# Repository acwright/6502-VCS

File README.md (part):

6502-VCS
========

An **AC6502** retro-style 8-bit computer based on the **65C02** microprocessor.

> 📖 **Guide:** [AC6502 Documentation](https://acwright.github.io/6502-DOCS/) — the user's and programmer's guide for the whole family.
> See [VCS's page in the family appendix](https://acwright.github.io/6502-DOCS/family/vcs).

---

**Building one? Every part you need, with supplier numbers and known issues, is in [BOM.md](BOM.md).**

## Table of Contents

- [Overview](#overview)
- [Architecture](#architecture)
- [Systems](#systems)
- [Software](#software)
- [Hardware](#hardware)
  - [Main Board](#main-board)
  - [Input Board](#input-board)
  - [Output Board](#output-board)
  - [ROM Cart](#rom-cart)
  - [Flash Cart](#flash-cart)
  - [Flash Helper](#flash-helper)
- [Which revision to make](#which-revision-to-make)
- [Firmware](#firmware)
  - [IB Controller](#ib-controller)
- [CAD](#cad)
- [Production](#production)
- [Schematics](#schematics)
- [Shared lines](#shared-lines)
- [Extra pins: `EXP0`–`EXP3` and `HRDB`](#extra-pins-exp0exp3-and-hrdb)
- [Jumpers](#jumpers)
- [Off-board headers](#off-board-headers)
- [Libraries](#libraries)
- [Bill of Materials](#bill-of-materials)
- [License](#license)

---

## Overview

The AC6502 ecosystem is a family of open-source, 65C02-based computers sharing a common architecture, memory map, and [BIOS](https://github.com/acwright/6502-BIOS). Each computer in the family is purpose-built for a different use case but runs the same software and firmware.

The **VCS** is a cartridge-based retro gaming console. It features a real 65C02 CPU, swappable ROM cartridges, VGA video output via [Pico9918](https://github.com/visrealm/pico9918), SID audio via ARMSID, and support for PS/2 keyboards, matrix keyboards, and Atari 2600-compatible joysticks.

## Architecture

All AC6502 computers share:

- **CPU**: 65C02 (or accurate emulation)
- **Memory**: 32KB RAM + 32KB ROM, with optional banked RAM expansion
- **Memory Map**: Standardized across the ecosystem — zero page, stack, I/O space ($8000–$9FFF), system ROM, and interrupt vectors at $FFFA–$FFFF
- **Bus**: 16-bit address bus, 8-bit bidirectional data bus, standard 65C02 control signals (RW, PHI2, RESET, IRQ, NMI, RDY, SYNC)
- **BIOS**: A common [BIOS](https://github.com/acwright/6502-BIOS) provides the kernel, monitor, and BASIC interpreter across all systems

## Systems

| Project | Description |
|---------|-------------|
| [6502-ACE](https://github.com/acwright/6502-ACE) | All-in-one Computer Experience — A single board computer |
| [6502-COB](https://github.com/acwright/6502-COB) | Computer On a Backplane — Modular desktop computer with expandable card slots |
| [6502-DEV](https://github.com/acwright/6502-DEV) | Development Environment Vehicle — Emulation-based dev system |
| [6502-KIM](https://github.com/acwright/6502-KIM) | Keypad Input Monitor - KIM-1 inspired minimal computer |
| [6502-VCS](https://github.com/acwright/6502-VCS) | Video Computer System — Cartridge-based retro gaming console (YOU ARE HERE) |

## Software

| Project | Description |
|---------|-------------|
| [6502-BIOS](https://github.com/acwright/6502-BIOS) | The shared BIOS (kernel, monitor, BASIC) for all AC6502 computers |
| [6502-EMULATOR](https://github.com/acwright/6502-EMULATOR) | Emulator for the whole family — desktop app, browser build, and a command line for scripted runs |
| [6502-PRG](https://github.com/acwright/6502-PRG) | Template project for writing assembly language programs |
| [6502-CRT](https://github.com/acwright/6502-CRT) | Template project for writing assembly language cartridges |
| [6502-ASM](https://github.com/acwright/6502-ASM) | Assembly language example programs and demos |
| [6502-BAS](https://github.com/acwright/6502-BAS) | BASIC program listings |
| [6502-WOZMON](https://github.com/acwright/6502-WOZMON) | Wozmon as a standalone ROM |
| [6502-NOP](https://github.com/acwright/6502-NOP) | An all-NOP ROM, for probing a board during bring-up |
| [6502-DOCS](https://github.com/acwright/6502-DOCS) | The documentation site — the guide, the printable reference cards, branding and label artwork |
| [cffs](https://github.com/acwright/cffs) | Builds CompactFlash disk images for the BIOS filesystem |
| [bastok](https://github.com/acwright/bastok) | Tokenizes BASIC listings into `.prg` images, and back |
| [bin2woz](https://github.com/acwright/bin2woz) | Converts a binary into a Wozmon serial upload |

## Hardware

This repository contains KiCad 7.0+ PCB designs for the boards that make up the VCS system.

### Main Board
`Hardware/Main Board/`

The core board containing the 65C02 CPU, 32KB SRAM, 32KB EEPROM, clock, and reset circuitry. Runs at 1 MHz and provides the bus connection for the Input and Output boards.

### Input Board
`Hardware/Input Board/`

Unified input board supporting a matrix keyboard, PS/2 keyboard, and Atari 2600-compatible joysticks. Uses a 65C22 VIA and an ATmega1284 microcontroller as the keyboard encoder controller.

The joysticks share the VIA ports with the keyboard encoder rather than having connectors of their own: they come in on the `J1` PORT B and `J2` PORT A box headers, with `JOY(1)` reading PORT B and `JOY(2)` reading PORT A. See [Joystick Interface](./Firmware/IB%20Controller/README.md#joystick-interface) for the wiring options and the bitmask the BIOS returns.

### Output Board
`Hardware/Output Board/`

Combined VGA video output (via Raspberry Pi Pico running [Pico9918](https://github.com/visrealm/pico9918)) and SID audio output (via ARMSID). Provides TMS9918A-compatible graphics modes at 640×480 VGA and 3-voice SID synthesis.

### ROM Cart
`Hardware/ROM Cart/`

Swappable ROM cartridge for the VCS system. Rev 1.0 came in two versions, one for each ROM chip:

- **Rev 1.0a** — Uses the **28C256** 32KB EEPROM (electrically erasable, no UV eraser required).
- **Rev 1.0b** — Uses the **27C256** 32KB EPROM (UV-erasable).

**Rev 1.1** (drawn, not yet made) takes either chip. Two solder jumpers, JP1 and JP2, ship set for the 28C256
(`28C`); cut and re-bridge both to `27C` for a 27C256. It also has an option for tinkerers, not fitted:
J2, `ROM BANK`, picks the chip's upper 16K (`HI`, as made) or its lower 16K (`LO`), so one chip can hold two
programs. See *Jumpers* below and the build notes in `BOM.md`.

### Flash Cart
`Hardware/Flash Cart/`

Banked flash cartridge, and the successor to the fixed 16K ROM Cart. One all-SMD board covers 128KB to 1MB,
depending on which parts are populated, and the flash is programmed in circuit through the card edge, either by
the Flash Helper (an Arduino Mega 2560 shield with one connector on it) or by the 6502 itself.

- `$C000–$DFFF` is a switchable 8K window, selected by a write-only bank register at `$E000–$FFFF`.
- `$E000–$FFFF` is fixed to the last 8K of the primary flash, so the vectors and the bank-switching code can
  never be mapped out.
- Existing 16K cart images run unmodified.
- **Tested in the 512KB and 1MB builds** (2026-11-09): programmed through the Flash Helper, and run on an ACE,
  banking into both chips and saving across a power cycle. The 128KB and 256KB builds (SST39SF010A, SST39SF020A)
  use the same board but haven't been built yet.
- Its 0.5 mm TSOP parts make it the hardest board in the family to build by hand: having JLCPCB assemble it is the
  preferred way to get one. See the build notes in [BOM.md](BOM.md#build-notes).

See [DESIGN.md](./Hardware/Flash%20Cart/Rev%201.0/DESIGN.md) for the memory map, the logic, the programming
sequences and the build variants.

### Flash Helper
`Hardware/Flash Helper/`

The programmer for the Flash Cart: an Arduino Mega 2560 R3 shield with a cartridge slot on it, and
nothing else. It pretends to be the 65C02 on the far side of the card edge, so a cart is programmed
in circuit with no chip ever removed — which matters, because the flash is a soldered-down TSOP part.

- Two parts: the Arduino, and the same TE card edge connector the Main Board fits as J9.
- Thirty-seven of the forty card edge pins: `A0–A15`, `D0–D7`, `RWB`, `PHI2`, `RESB`, `IRQB`, `NMIB`,
  `VCC` and `GND`.
- `EXP0` and `EXP1` are deliberately **not** connected. Cartridges tie them to GND to disable the
  system ROM, so driving them would be a short.
- Host side is `6502-flash`, a Node CLI. See [DESIGN.md](./Hardware/Flash%20Cart/Rev%201.0/DESIGN.md).

**As a card tester.** Every card in the AC6502 family — the [COB](https://github.com/acwright/6502-COB)
cards, the [KIM](https://github.com/acwright/6502-KIM) Keypad Card and both VCS carts — carries the same
`6502 Card Edge` fingers and drops into this socket. `IRQB` and `NMIB` are wired for that reason rather
than for programming: the GPIO, LCD, Serial and Serial Card Pro cards all assert `IRQB`, and a tester
that could not see it would miss most of what they do. That firmware is a separate build and does not
exist yet.

<!-- Which revision to make: generated by Tools/revision-audit/register.py from Tools/data/orders.json. Edit that file, not this section. -->
## Which revision to make

**Make the newest revision of a board, and check its label first.** The table below gives each board's newest revision. A newer revision fixes what was found on the older ones. Every revision, old and new, is in [REVISIONS.md](REVISIONS.md), with what changed in each.

Each revision carries one of three labels:

- **Tested:** This revision was built and tested.
- **Proven design:** Not built at this revision, but its circuit is a tested revision's. The only changes are silkscreen text, part values, mounting holes, outline clean-up, parts moved a fraction of a millimetre onto their grid, capacitor pitch, socket outlines, a footprint swap with the same holes, a solder jumper's default, the solder mask or paste at a card edge, or tracks rerouted or pours refilled with DRC and the netlist check passing. A builder can treat it as tested.
- **Untested:** The circuit, the power path or the layout changed in a way that only a built board proves, or the board has never been built at all.

[BOM.md](BOM.md) has the parts for every revision, and its known issues.

| Board | Newest revision | Label | Why |
|---|---|---|---|
| Flash Cart | 1.1 | **Proven design** | The bare card edge and the shell's holes at their nominal places. |
| Flash Helper | 1.1 | **Proven design** | J1's reference resized and the logo moved; silkscreen only. |
| Input Board | 1.1 | **Proven design** | Silkscreen text only. |
| Main Board | 1.1 | **Proven design** | 10k pull-ups, small part moves and tracks rerouted, and a 74HCT00 at U5. The jumpers are gone, and `HRDB` is wired as it is on the tested Rev 1.0 with them fitted. |
| Output Board | 1.1 | **Proven design** | Silkscreen text, the `VDD` header removed, JP1 ships open, and JP2 and JP3 removed and wired as Rev 1.0 ships them. |
| ROM Cart | 1.1 | **Proven design** | Either ROM chip through two solder jumpers, each setting a tested board's wiring; a ROM bank option, not fitted, whose pull-up reads the half Rev 1.0 reads; capacitor pitch; the bare card edge and the shell's holes at their nominal places. |
<!-- End of which revision to make -->

## Firmware

This repository contains [PlatformIO](https://platformio.org/)-based firmware for the Input Board.

### IB Controller
`Firmware/IB Controller/`

Firmware for the ATmega1284 on the Input Board. Provides:

- Matrix keyboard scanning and encoding
- PS/2 keyboard interface
- Atari 2600-compatible joystick input
- Parallel I/O to the AC6502 bus via 65C22 VIA

See [Firmware/IB Controller/README.md](./Firmware/IB%20Controller/README.md) for setup and usage instructions.

## CAD
`CAD/`

3D-printable enclosure parts and laser-cut top panels for the VCS system.

**Board images** are in `CAD/Images/<Board>/Rev X/`: `Front.png` and `Back.png` on white, and `Front Transparent.png` and `Back Transparent.png` with no background. Every image is a 3D render at the same size, with the black solder mask and white silkscreen the boards are made with. Bare-board photos may differ, because the renders show parts fitted.

**Top panels are versioned by board revision**, like `Hardware/`: `CAD/Tops/<Board>/Rev X/`. Each revision has its own complete folder, even when two revisions share the same files. `Bases/` holds the parts for a whole computer, not for one board, so it isn't versioned.

The **[plate mounting drawing](CAD/Bases/Plate%20Mounting%20Drawing.png)** ([SVG](CAD/Bases/Plate%20Mounting%20Drawing.svg)) shows where the Output Board, the Main Board and the Input Board mount on the base plate, with every hole's position and the hardware the build needs. The plate is a stack of three 3 mm acrylic layers.

## Production
`Production/`

[REVISIONS.md](REVISIONS.md) lists every board revision: whether it was made, its JLCPCB order, the commit it was made from, and what fits it.

JLCPCB-ready Gerber files and BOM/CPL for PCB fabrication and assembly.

## Schematics
`Schematics/`

PDF schematics for each board.

## Shared lines

Five lines of the 6502 bus are shared by every board on it: `RESB`, `IRQB`, `NMIB`, `RDY` and `BE`. A board may pull one of these lines low, and nothing drives one high. Each line is held high by one 10kΩ pull-up resistor to VCC, on the board with the CPU: the ACE Board, the KIM Board, the VCS Main Board, the COB CPU Card or CPU Card Pro, or the DEV Board. No other board has one. Two pull-ups on the same line would sit in parallel and lower its resistance, so a card that adds its own pull-up changes the machine for every other board. The VIAs and PIAs in the BOMs, the W65C22N and W65C21N, have open-drain interrupt outputs for this reason.

**Interrupt outputs.** Whatever drives `IRQB` or `NMIB` may only pull it low. Every board is drawn for the parts in its BOM and works as shipped, with no jumper to cut or bridge:

- **A part whose interrupt output is open-drain** (the W65C22N, W65C21N, R6551AP, DS1511Y and TMS9918A) drives the line directly, or through a diode with a solder jumper across it that ships bridged. The diode is fitted either way. To use a part that drives its interrupt high as well as low instead, such as a W65C22S or a replacement of your own, cut the jumper: the diode then lets the part only pull the line low. A board with no diode in the line can't take such a part.
- **A part that drives its interrupt high as well as low** (the pico9918, the VERA module, and a microcontroller such as the ATmega1284 or a Raspberry Pi Pico) reaches the line through a diode, a BAT85 or a 1N914, with its cathode toward the part. Where a solder jumper sits across that diode, it ships open. The diode is then the only path to the line, so fit it, and never bridge the jumper, because the part would then hold the line high against every other interrupt source.
- **A microcontroller wired to the line directly,** as on the ACE Board, the Mega Helper and the Flash Helper, drives it open-drain in its firmware: it sets the pin low or leaves it as an input, and never drives it high.

The *Jumpers* section below gives each board's interrupt jumper.

The same holds where a board has its own reset circuit. A reset switch, its timer and the transistor that pulls `RESB` low can be on any board, such as the COB Backplane Pro or the Clock Card, but the `RESB` pull-up is only ever on the board with the CPU. Each of those boards draws its pull-ups together, in one group on its schematic.

The DEV Board is the exception on `RESB`. It stands in for a Main Board, so it owns reset: its Reset button goes to the Teensy, and the Teensy drives `RESB` onto the bus through U3, a level shifter that only sends signals out, as it drives `PHI2`. U3 holds `RESB` high or low, so the DEV Board has no `RESB` pull-up, and nothing else on its bus may pull `RESB` low. Connect a DEV only to a passive backplane, never to the COB Backplane Pro, whose reset circuit would pull against U3, and don't fit a card that pulls `RESB` low, such as the COB RTC Card.

`SOB` is a CPU pin that isn't on the bus. It is tied to VCC, directly or through a 10kΩ resistor.

A few chips have a pull-up of their own inside the chip, such as an ATmega's reset pin. Where such a pin is wired to `RESB`, its pull-up of 30–60kΩ sits in parallel with the 10kΩ one. That's harmless, because whatever pulls `RESB` low can sink the extra current many times over.

A revision that doesn't follow this yet says so in its known issues in [BOM.md](BOM.md), with what to fit or remove.

## Extra pins: `EXP0`–`EXP3` and `HRDB`

`EXP` stands for "extra pin". Four pins of the 6502 bus are left for a builder's own use: pin 4 is `EXP1`, pin 6 is `EXP0`, pin 19 is `EXP3` and pin 21 is `EXP2`.

Pins 4 and 6 have a second job. A cartridge ties both of them to GND. That pulls `HRDB` ("High ROM disable bar", active low) low on the board with the ROM, which takes `$C000–$FFFF` away from the ROM so that the cartridge answers there instead. So in a build that uses cartridges, pins 4 and 6 are reserved for `HRDB`, and nothing else may drive them. They are free as `EXP1` and `EXP0` only in a build that never uses cartridges. `EXP2` and `EXP3` are always free.

How the boards treat pins 4 and 6:

- **The ACE Board and the KIM Board** join them to their ROM's `HRDB` input, and their silk says `HRDB`. The VCS Main Board joins them the same way from Rev 1.1.
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
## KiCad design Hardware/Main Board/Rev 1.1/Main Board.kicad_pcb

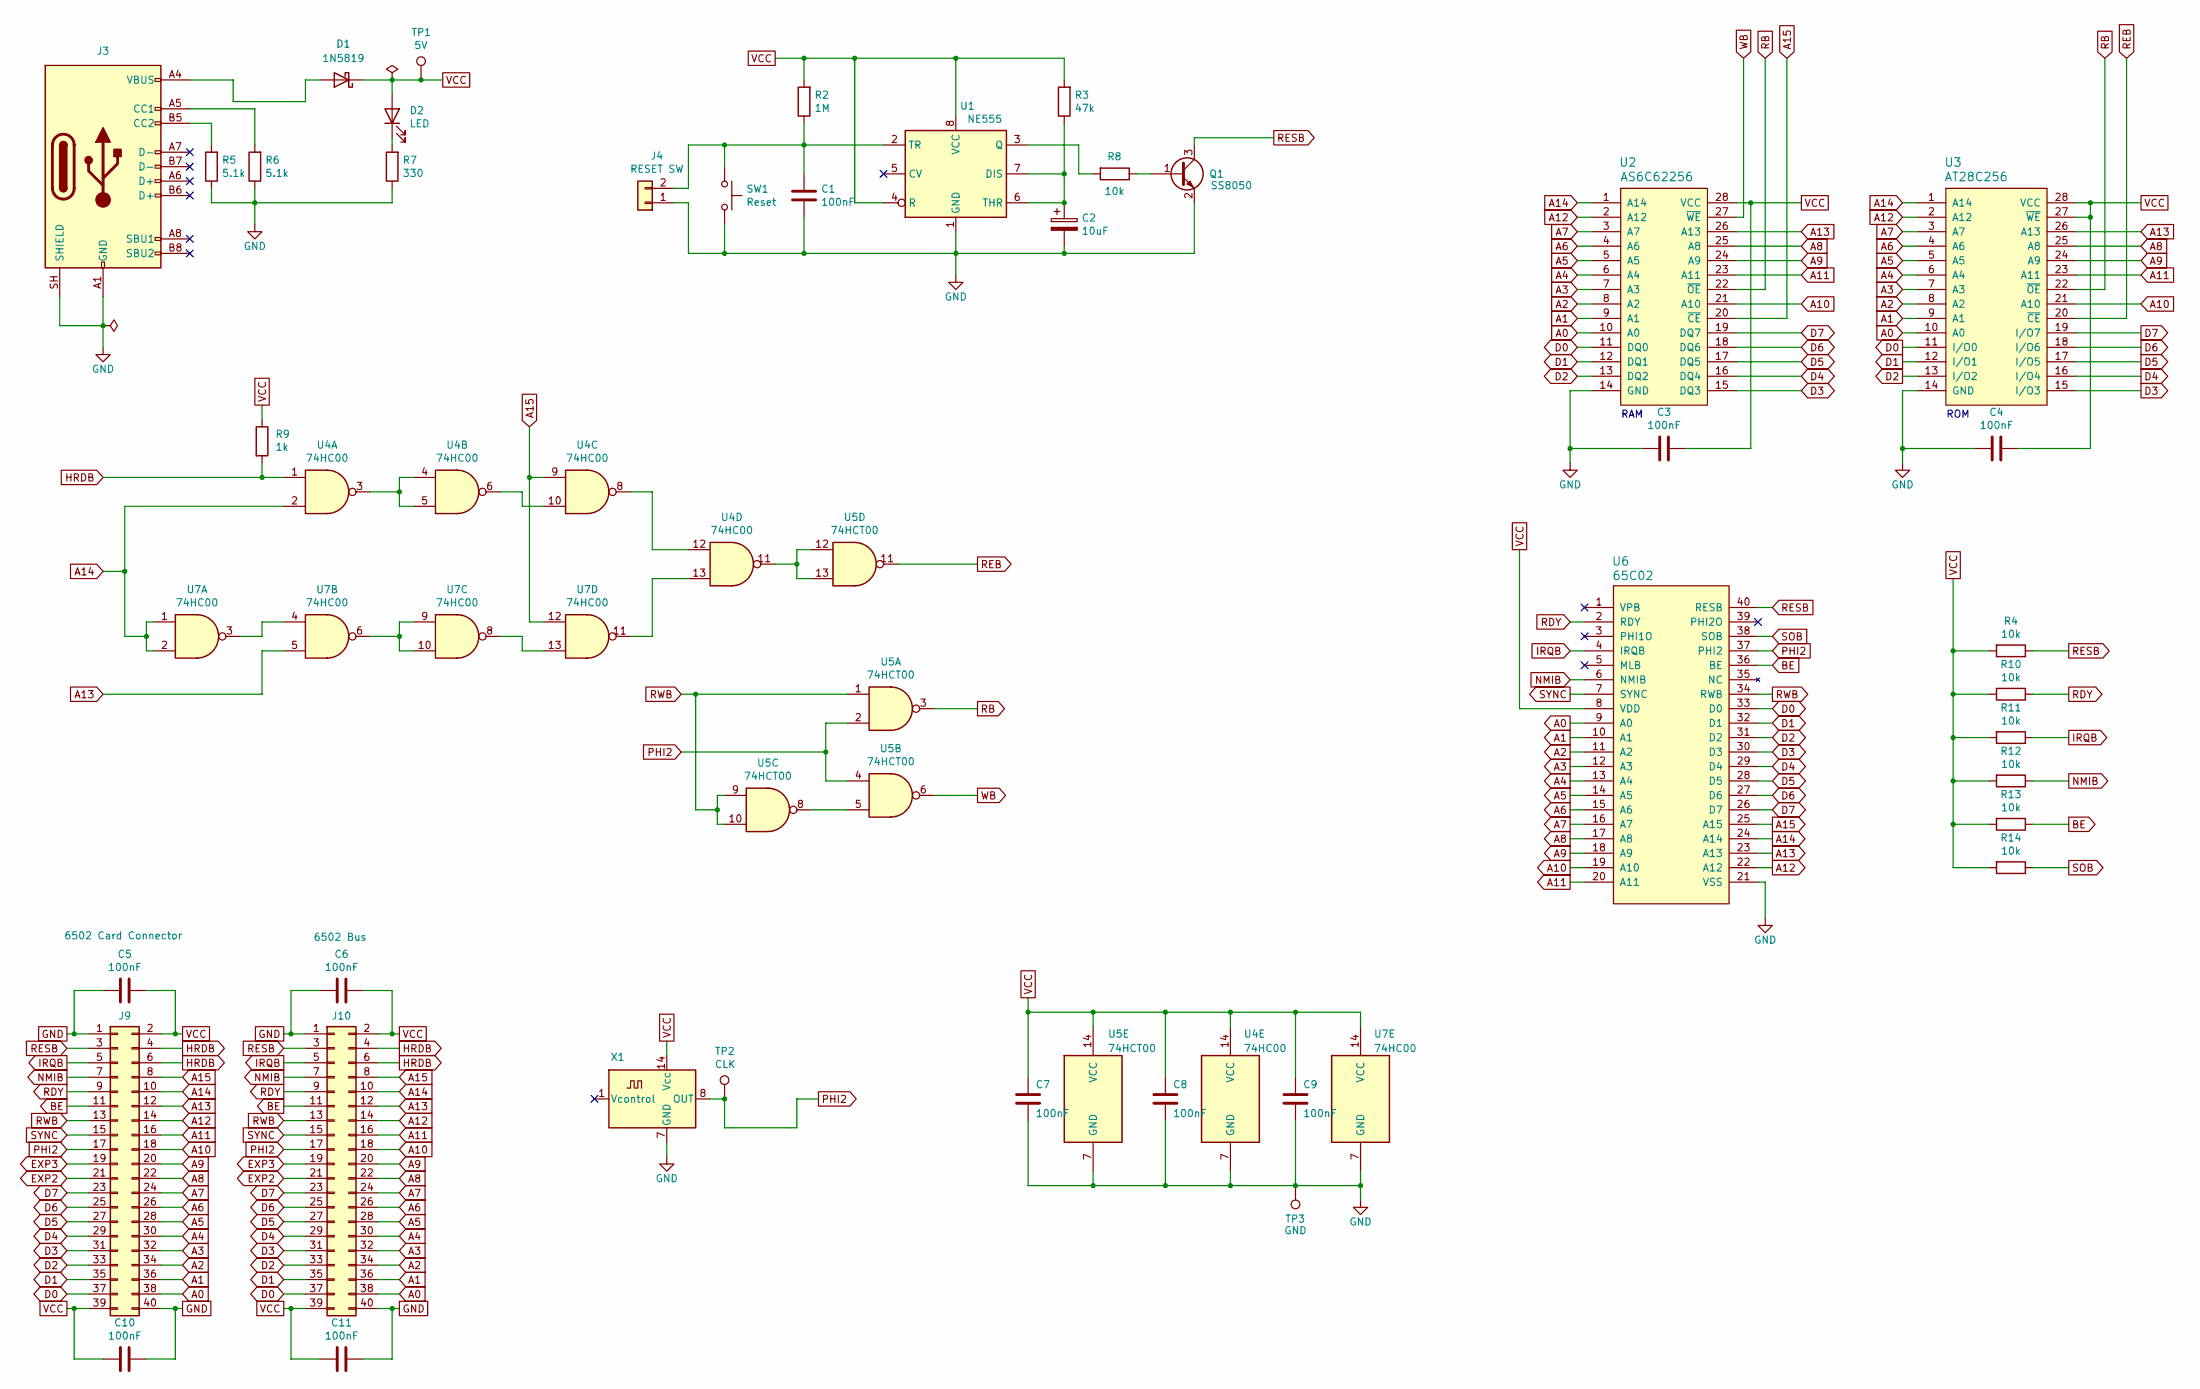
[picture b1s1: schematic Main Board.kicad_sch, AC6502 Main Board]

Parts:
C1, C3, C4, C5, C6, C7, C8, C9, C10, C11: 100nF; C_0805_2012Metric; LCSC C49678
C2: 10uF; C_1206_3216Metric; LCSC C7171
D1: 1N5819; D_SOD-323F; LCSC C191023
D2: LED; LED_0805_2012Metric; LCSC C2297
J3: USB_C_Receptacle_USB2.0; USB_C_Receptacle_HRO_TYPE-C-31-M-12; LCSC C2988369
J4: RESET SW; JST_XH_B2B-XH-A_1x02_P2.50mm_Vertical; Digikey 455-B2B-XH-A-ND
J9: 6502 Card Connector; 6502 Card Slot; Mouser 571-5-5530843-4
J10: 6502 Bus; 6502 Bus Connector; Digikey 732-5401-ND
Q1: SS8050; SOT-23; LCSC C2150
R2: 1M; R_0805_2012Metric; LCSC C17514
R3: 47k; R_0805_2012Metric; LCSC C17713
R4, R8, R10, R11, R12, R13, R14: 10k; R_0805_2012Metric; LCSC C17414
R5, R6: 5.1k; R_0805_2012Metric; LCSC C27834
R7: 330; R_0805_2012Metric; LCSC C17630
R9: 1k; R_0805_2012Metric; LCSC C17513
SW1: Reset; Tact Switch SMD 5.1mm; LCSC C318884
TP1: 5V; TestPoint_Pad_1.0x1.0mm
TP2: CLK; TestPoint_Pad_1.0x1.0mm
TP3: GND; TestPoint_Pad_1.0x1.0mm
U1: NE555; SOIC-8_3.9x4.9mm_P1.27mm; LCSC C7593
U2: AS6C62256; DIP-28_W15.24mm_Socket_LongPads; Digikey 1450-1033-ND
U3: AT28C256; DIP_Socket-28_W11.9mm_W12.7mm_W15.24mm_W17.78mm_W18.5mm_3M_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; Digikey AT28C256-15PU-ND
U4, U7: 74HC00; SOIC-14_3.9x8.7mm_P1.27mm; LCSC C5586
U5: 74HCT00; SOIC-14_3.9x8.7mm_P1.27mm; LCSC C6764
U6: 65C02; DIP-40_W15.24mm_Socket_LongPads; Mouser 955-W65C02S6TPG-14
X1: 1 MHz; Oscillator_DIP-14; Digikey X937-ND

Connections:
A0: J9.38, J10.38, U2.10 (A0), U3.10 (A0), U6.9 (A0)
A1: J9.36, J10.36, U2.9 (A1), U3.9 (A1), U6.10 (A1)
A2: J9.34, J10.34, U2.8 (A2), U3.8 (A2), U6.11 (A2)
A3: J9.32, J10.32, U2.7 (A3), U3.7 (A3), U6.12 (A3)
A4: J9.30, J10.30, U2.6 (A4), U3.6 (A4), U6.13 (A4)
A5: J9.28, J10.28, U2.5 (A5), U3.5 (A5), U6.14 (A5)
A6: J9.26, J10.26, U2.4 (A6), U3.4 (A6), U6.15 (A6)
A7: J9.24, J10.24, U2.3 (A7), U3.3 (A7), U6.16 (A7)
A8: J9.22, J10.22, U2.25 (A8), U3.25 (A8), U6.17 (A8)
A9: J9.20, J10.20, U2.24 (A9), U3.24 (A9), U6.18 (A9)
A10: J9.18, J10.18, U2.21 (A10), U3.21 (A10), U6.19 (A10)
A11: J9.16, J10.16, U2.23 (A11), U3.23 (A11), U6.20 (A11)
A12: J9.14, J10.14, U2.2 (A12), U3.2 (A12), U6.22 (A12)
A13: J9.12, J10.12, U2.26 (A13), U3.26 (A13), U6.23 (A13), U7.5
A14: J9.10, J10.10, U2.1 (A14), U3.1 (A14), U4.2, U6.24 (A14), U7.1, U7.2
A15: J9.8, J10.8, U2.20 (~CE), U4.9, U6.25 (A15), U7.12
BE: J9.11, J10.11, R13.1, U6.36 (BE)
D0: J9.37, J10.37, U2.11 (DQ0), U3.11 (I/O0), U6.33 (D0)
D1: J9.35, J10.35, U2.12 (DQ1), U3.12 (I/O1), U6.32 (D1)
D2: J9.33, J10.33, U2.13 (DQ2), U3.13 (I/O2), U6.31 (D2)
D3: J9.31, J10.31, U2.15 (DQ3), U3.15 (I/O3), U6.30 (D3)
D4: J9.29, J10.29, U2.16 (DQ4), U3.16 (I/O4), U6.29 (D4)
D5: J9.27, J10.27, U2.17 (DQ5), U3.17 (I/O5), U6.28 (D5)
D6: J9.25, J10.25, U2.18 (DQ6), U3.18 (I/O6), U6.27 (D6)
D7: J9.23, J10.23, U2.19 (DQ7), U3.19 (I/O7), U6.26 (D7)
EXP2: J9.21, J10.21
EXP3: J9.19, J10.19
GND: C1.2, C2.2, C3.2, C4.2, C5.2, C6.2, C7.2, C8.2, C9.2, C10.1, C11.1, J3.A1 (GND), J3.A12 (GND), J3.B1 (GND), J3.B12 (GND), J3.SH (SHIELD), J4.1, J9.1, J9.40, J10.1, J10.40, Q1.2 (E), R5.1, R6.1, R7.1, SW1.2, TP3.1 (1_1), U1.1 (GND), U2.14 (GND), U3.14 (GND), U4.7 (GND), U5.7 (GND), U6.21 (VSS), U7.7 (GND), X1.7 (GND)
HRDB: J9.4, J9.6, J10.4, J10.6, R9.2, U4.1
IRQB: J9.5, J10.5, R11.1, U6.4 (IRQB)
NMIB: J9.7, J10.7, R12.1, U6.6 (NMIB)
unnamed: D1.2 (A), J3.A4 (VBUS), J3.A9 (VBUS), J3.B4 (VBUS), J3.B9 (VBUS)
unnamed: D2.1 (K), R7.2
unnamed: J3.A5 (CC1), R6.2
unnamed: J3.B5 (CC2), R5.2
unnamed: C1.1, J4.2, R2.1, SW1.1, U1.2 (TR)
unnamed: Q1.1 (B), R8.1
unnamed: C2.1, R3.1, U1.6 (THR), U1.7 (DIS)
unnamed: R8.2, U1.3 (Q)
unnamed: U4.3, U4.4, U4.5
unnamed: U4.6, U4.10
unnamed: U4.11, U5.12, U5.13
unnamed: U4.8, U4.12
unnamed: U4.13, U7.11
unnamed: U5.5, U5.8
unnamed: U7.3, U7.4
unnamed: U7.6, U7.9, U7.10
unnamed: U7.8, U7.13
PHI2: J9.17, J10.17, TP2.1 (1_1), U5.2, U5.4, U6.37 (PHI2), X1.8 (OUT)
RB: U2.22 (~OE), U3.22 (~OE), U5.3
RDY: J9.9, J10.9, R10.1, U6.2 (RDY)
REB: U3.20 (~CE), U5.11
RESB: J9.3, J10.3, Q1.3 (C), R4.1, U6.40 (RESB)
RWB: J9.13, J10.13, U5.1, U5.9, U5.10, U6.34 (RWB)
SOB: R14.1, U6.38 (SOB)
SYNC: J9.15, J10.15, U6.7 (SYNC)
VCC: C3.1, C4.1, C5.1, C6.1, C7.1, C8.1, C9.1, C10.2, C11.2, D1.1 (K), D2.2 (A), J9.2, J9.39, J10.2, J10.39, R2.2, R3.2, R4.2, R9.1, R10.2, R11.2, R12.2, R13.2, R14.2, TP1.1 (1_1), U1.4 (R), U1.8 (VCC), U2.28 (VCC), U3.27 (~WE), U3.28 (VCC), U4.14 (VCC), U5.14 (VCC), U6.8 (VDD), U7.14 (VCC), X1.14 (Vcc)
WB: U2.27 (~WE), U5.6

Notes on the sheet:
ROM
RAM

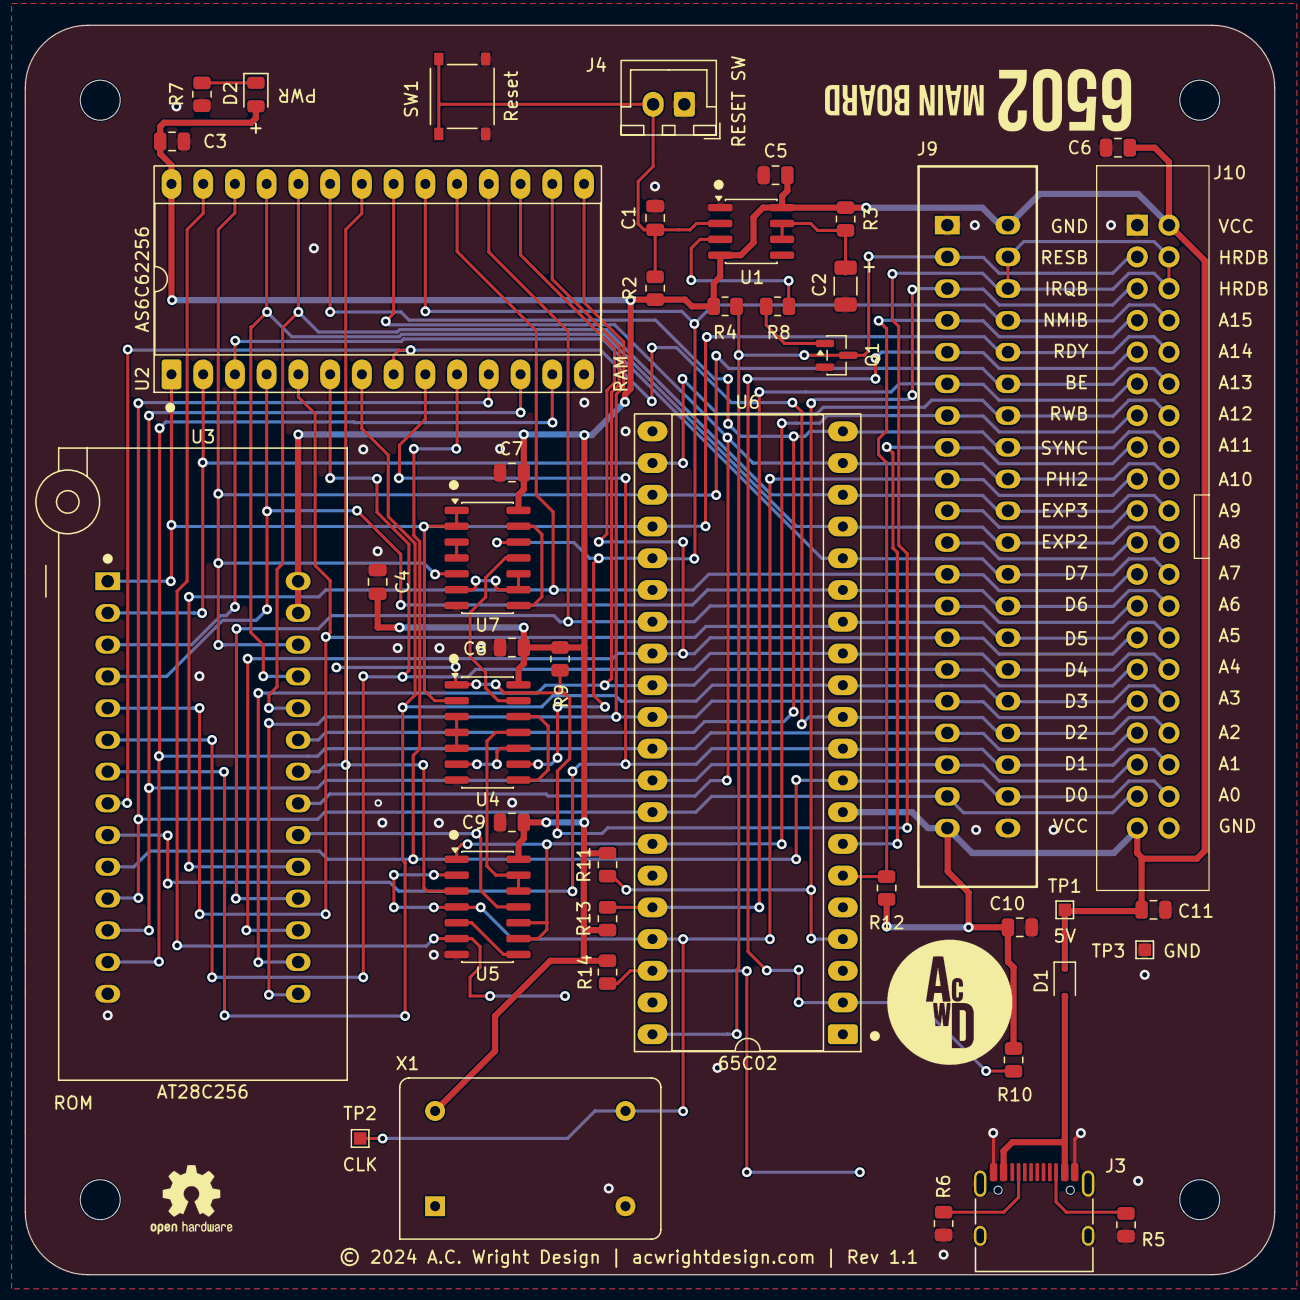
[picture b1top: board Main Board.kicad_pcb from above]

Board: 2 copper layers, 100.0 x 100.0 mm, 47 parts (0 on the bottom side), 58 nets.

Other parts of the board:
H1, H2, H3, H4: MountingHole; MountingHole_3.2mm_M3

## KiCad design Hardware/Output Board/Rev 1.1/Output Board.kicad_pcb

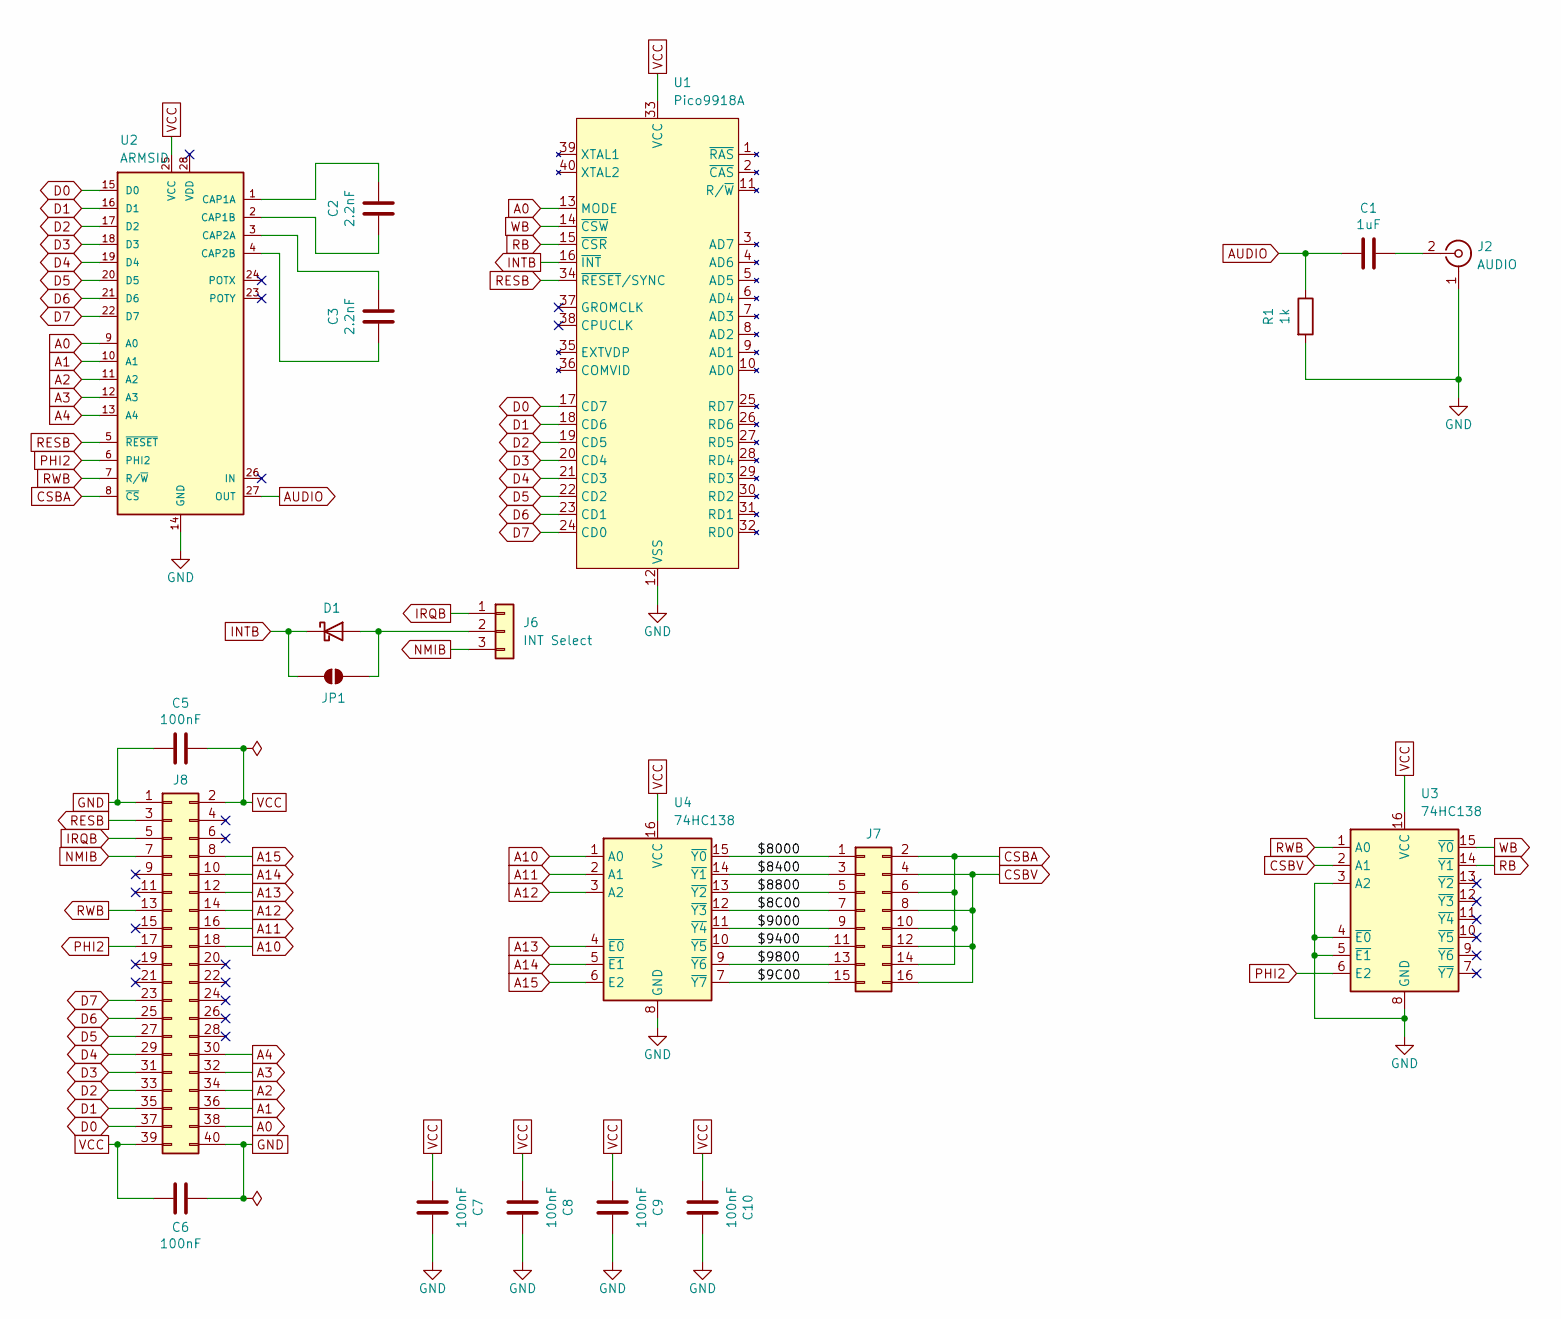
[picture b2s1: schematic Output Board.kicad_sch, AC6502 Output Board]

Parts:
C1: 1uF; C_0805_2012Metric; LCSC C28323
C2, C3: 2.2nF; C_0805_2012Metric; LCSC C28260
C5, C6, C7, C8, C9, C10: 100nF; C_0805_2012Metric; LCSC C49678
D1: 1N914; D_DO-35_SOD27_P7.62mm_Horizontal; Mouser 512-1N914
J2: AUDIO; RCA Jack White; Digikey PJRAN1X1U02X-ND
J6: INT Select; PinHeader_1x03_P2.54mm_Vertical; Mouser 200-TSW14007TS
J7: IO SELECT; PinHeader_2x08_P2.54mm_Vertical; Mouser 649-67996-140HLF
J8: 6502 Bus; 6502 Bus Connector; Mouser 710-61204021621
JP1: SolderJumper_2_Open; SolderJumper-2_P1.3mm_Open_RoundedPad1.0x1.5mm
R1: 1k; R_0805_2012Metric; LCSC C17513
U1: Pico9918A; DIP_Socket-40_W11.9mm_W12.7mm_W15.24mm_W17.78mm_W18.5mm_3M_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
U2: ARMSID; DIP_Socket-28_W11.9mm_W12.7mm_W15.24mm_W17.78mm_W18.5mm_3M_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
U3, U4: 74HC138; SOIC-16_3.9x9.9mm_P1.27mm; LCSC C5602

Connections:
/$8C00: J7.7, U4.12 (~Y3)
/$9C00: J7.15, U4.7 (~Y7)
/$8000: J7.1, U4.15 (~Y0)
/$8400: J7.3, U4.14 (~Y1)
/$8800: J7.5, U4.13 (~Y2)
/$9000: J7.9, U4.11 (~Y4)
/$9400: J7.11, U4.10 (~Y5)
/$9800: J7.13, U4.9 (~Y6)
A0: J8.38, U1.13 (MODE), U2.9 (A0)
A1: J8.36, U2.10 (A1)
A2: J8.34, U2.11 (A2)
A3: J8.32, U2.12 (A3)
A4: J8.30, U2.13 (A4)
A10: J8.18, U4.1 (A0)
A11: J8.16, U4.2 (A1)
A12: J8.14, U4.3 (A2)
A13: J8.12, U4.4 (~E0)
A14: J8.10, U4.5 (~E1)
A15: J8.8, U4.6 (E2)
AUDIO: C1.1, R1.1, U2.27 (OUT)
CSBA: J7.2, J7.6, J7.10, J7.14, U2.8 (~CS)
CSBV: J7.4, J7.8, J7.12, J7.16, U3.2 (A1)
D0: J8.37, U1.17 (CD7), U2.15 (D0)
D1: J8.35, U1.18 (CD6), U2.16 (D1)
D2: J8.33, U1.19 (CD5), U2.17 (D2)
D3: J8.31, U1.20 (CD4), U2.18 (D3)
D4: J8.29, U1.21 (CD3), U2.19 (D4)
D5: J8.27, U1.22 (CD2), U2.20 (D5)
D6: J8.25, U1.23 (CD1), U2.21 (D6)
D7: J8.23, U1.24 (CD0), U2.22 (D7)
GND: C5.2, C6.1, C7.2, C8.2, C9.2, C10.2, J2.1 (Ext), J8.1, J8.40, R1.2, U1.12 (VSS), U2.14 (GND), U3.3 (A2), U3.4 (~E0), U3.5 (~E1), U3.8 (GND), U4.8 (GND)
INTB: D1.1 (K), JP1.1 (A), U1.16 (~INT)
IRQB: J6.1, J8.5
NMIB: J6.3, J8.7
unnamed: D1.2 (A), J6.2, JP1.2 (B)
unnamed: C1.2, J2.2 (In)
unnamed: C2.2, U2.1 (CAP1A)
unnamed: C2.1, U2.2 (CAP1B)
unnamed: C3.2, U2.3 (CAP2A)
unnamed: C3.1, U2.4 (CAP2B)
PHI2: J8.17, U2.6 (PHI2), U3.6 (E2)
RB: U1.15 (~CSR), U3.14 (~Y1)
RESB: J8.3, U1.34 (~RESET/SYNC), U2.5 (~RESET)
RWB: J8.13, U2.7 (R/~W), U3.1 (A0)
VCC: C5.1, C6.2, C7.1, C8.1, C9.1, C10.1, J8.2, J8.39, U1.33 (VCC), U2.25 (VCC), U3.16 (VCC), U4.16 (VCC)
WB: U1.14 (~CSW), U3.15 (~Y0)

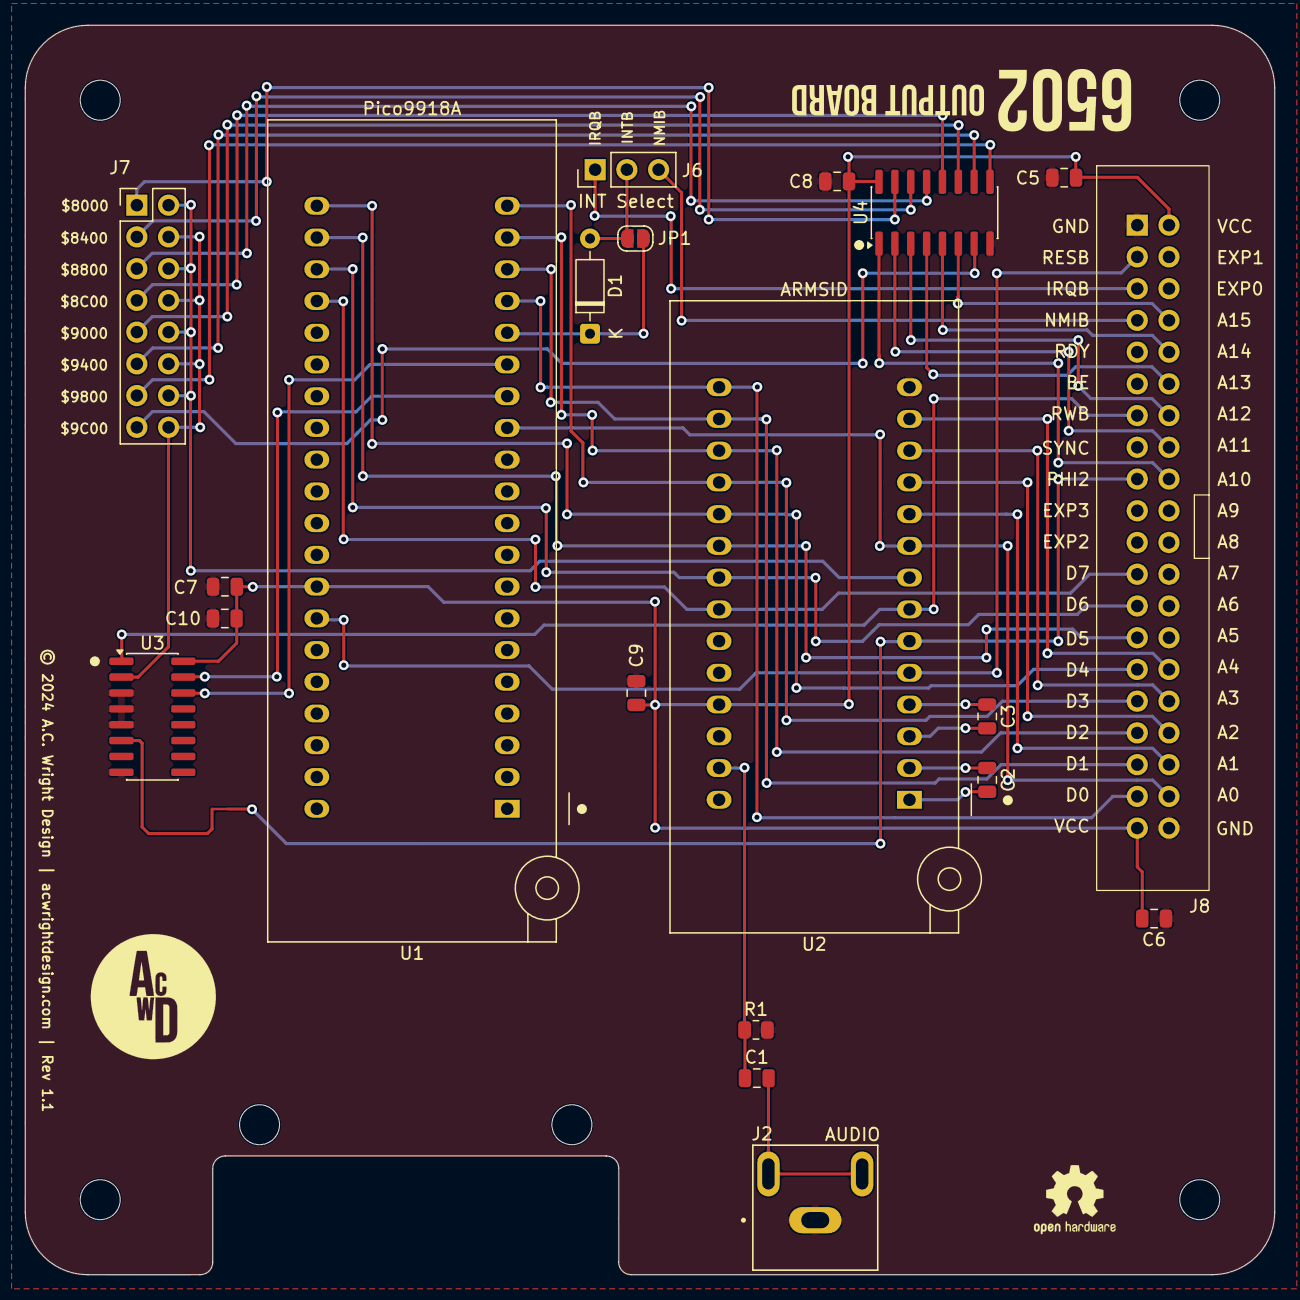
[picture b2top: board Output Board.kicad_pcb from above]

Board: 2 copper layers, 100.0 x 100.0 mm, 24 parts (0 on the bottom side), 46 nets.

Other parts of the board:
H1, H2, H3, H4: MountingHole; MountingHole_3.2mm_M3

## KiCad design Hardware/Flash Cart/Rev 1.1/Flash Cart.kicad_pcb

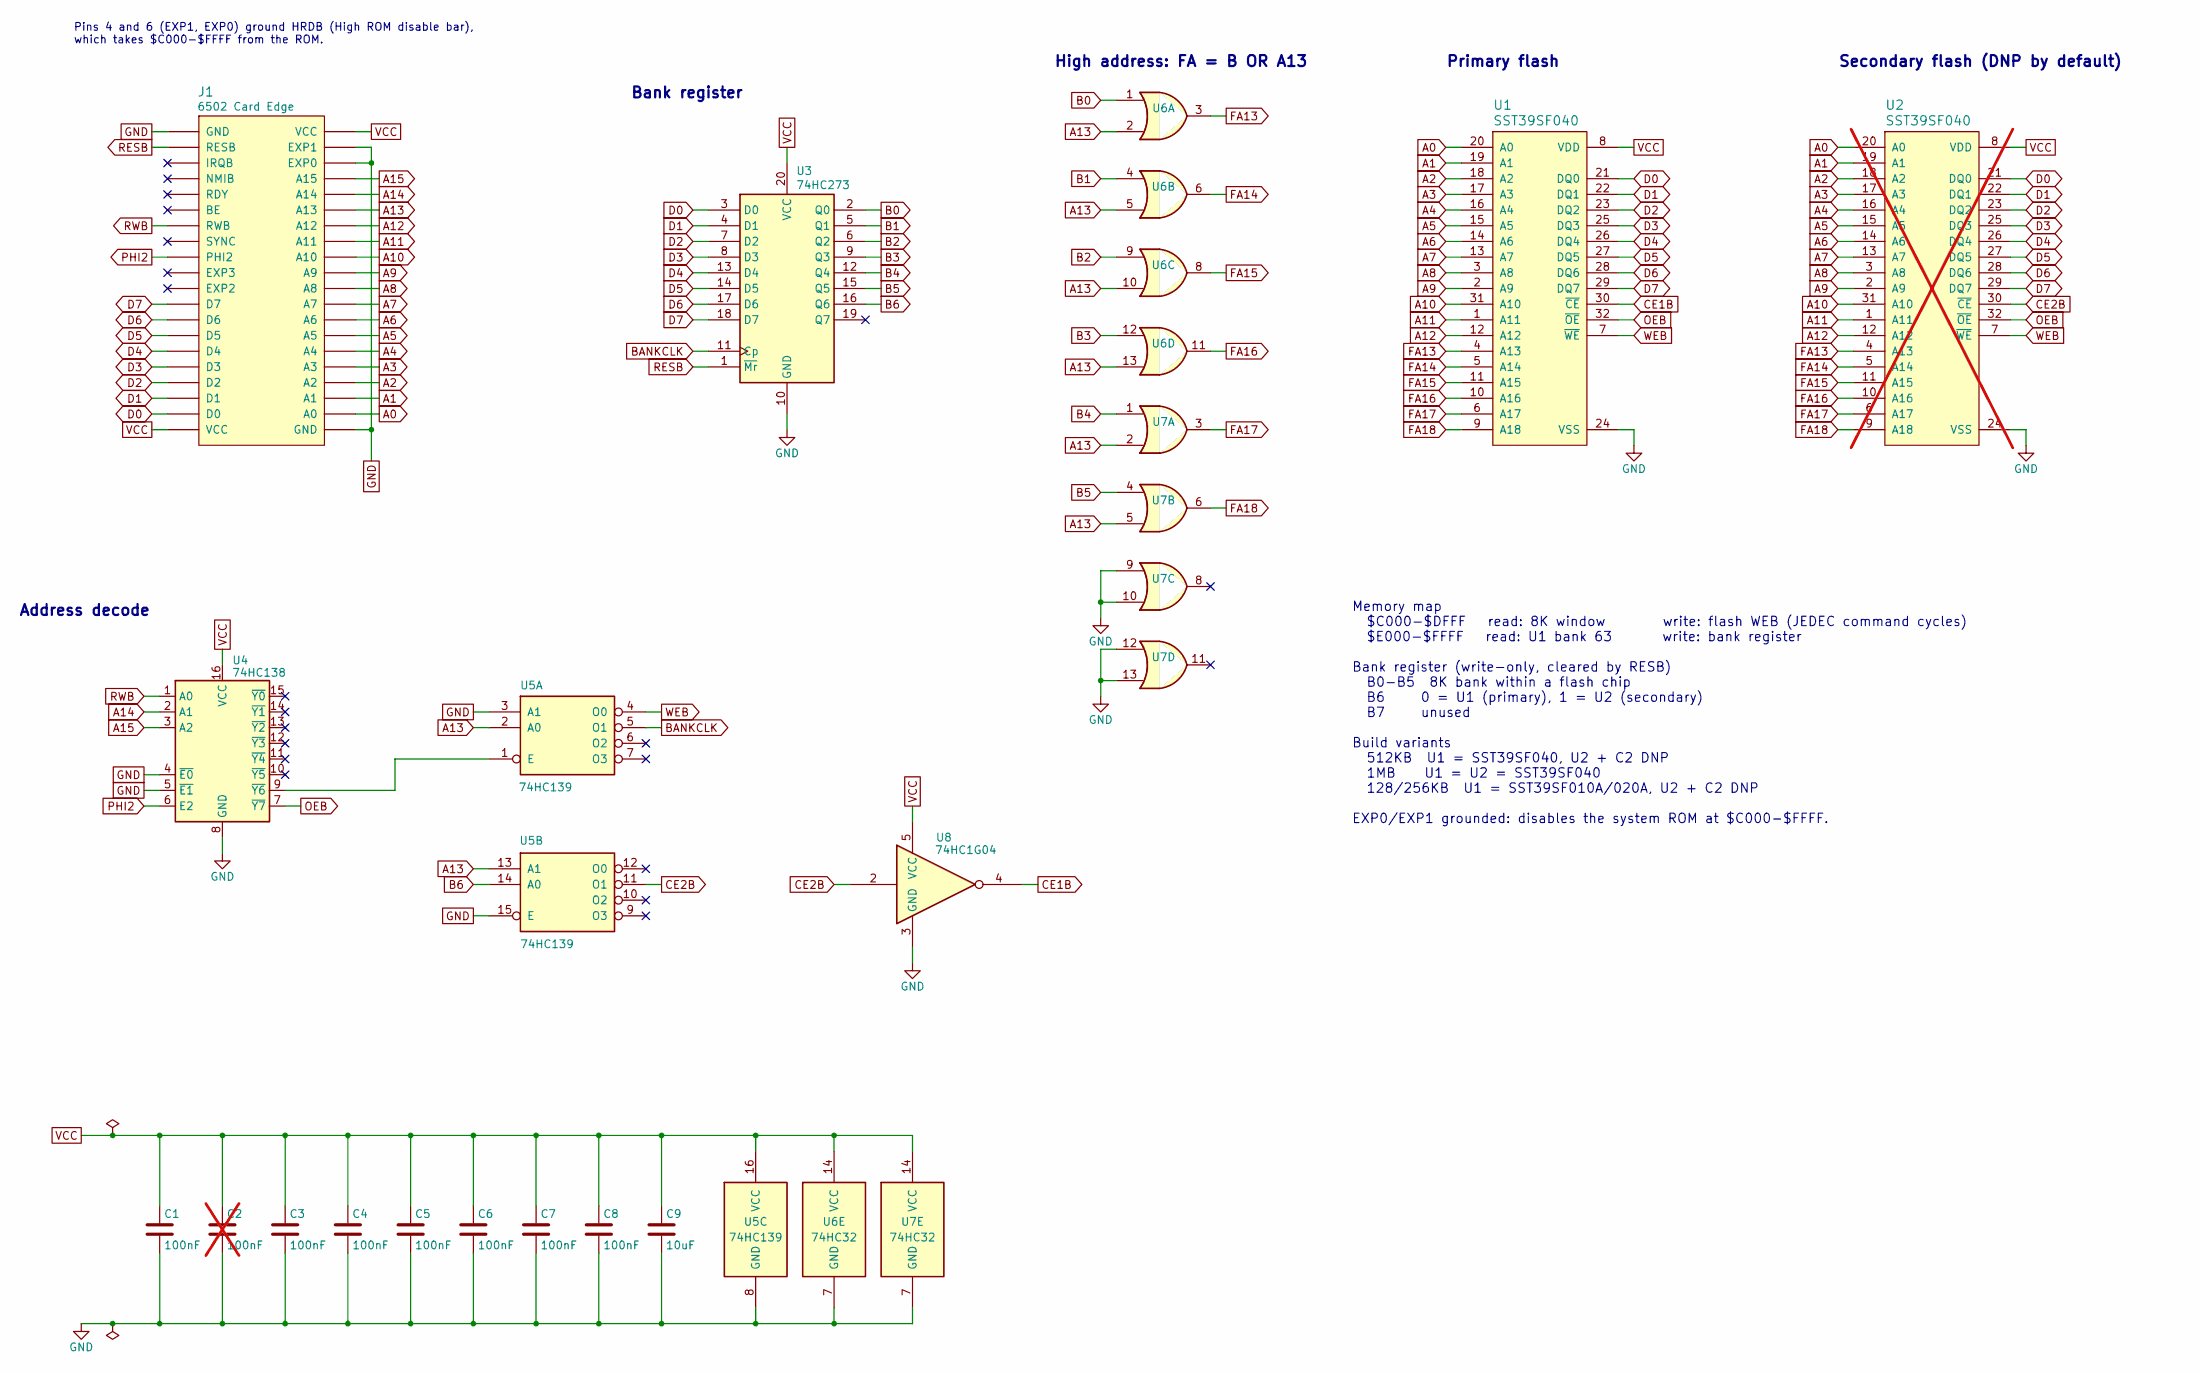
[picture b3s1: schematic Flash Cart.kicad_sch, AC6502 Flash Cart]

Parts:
C1, C3, C4, C5, C6, C7, C8: 100nF; C_0603_1608Metric; Digikey 399-C0603C104K5RACTUCT-ND
C2: 100nF; C_0603_1608Metric; Digikey 399-C0603C104K5RACTUCT-ND; not fitted
C9: 10uF; C_0805_2012Metric; Digikey 311-3502-1-ND
J1: 6502 Card Edge
U1: SST39SF040; TSOP-I-32_11.8x8mm_P0.5mm; Digikey 150-SST39SF040-70-4C-TU-ND
U2: SST39SF040; TSOP-I-32_11.8x8mm_P0.5mm; Digikey 150-SST39SF040-70-4C-TU-ND; not fitted
U3: 74HC273; SOIC-20W_7.5x12.8mm_P1.27mm; Digikey 1727-2795-1-ND
U4: 74HC138; SOIC-16_3.9x9.9mm_P1.27mm; Digikey 1727-2781-1-ND
U5: 74HC139; SOIC-16_3.9x9.9mm_P1.27mm; Digikey 1727-5943-1-ND
U6, U7: 74HC32; SOIC-14_3.9x8.7mm_P1.27mm; Digikey 1727-2797-1-ND
U8: 74HC1G04; SOT-23-5; Digikey 1727-6034-1-ND

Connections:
A0: J1.A0, U1.20 (A0), U2.20 (A0)
A1: J1.A1, U1.19 (A1), U2.19 (A1)
A2: J1.A2, U1.18 (A2), U2.18 (A2)
A3: J1.A3, U1.17 (A3), U2.17 (A3)
A4: J1.A4, U1.16 (A4), U2.16 (A4)
A5: J1.A5, U1.15 (A5), U2.15 (A5)
A6: J1.A6, U1.14 (A6), U2.14 (A6)
A7: J1.A7, U1.13 (A7), U2.13 (A7)
A8: J1.A8, U1.3 (A8), U2.3 (A8)
A9: J1.A9, U1.2 (A9), U2.2 (A9)
A10: J1.A10, U1.31 (A10), U2.31 (A10)
A11: J1.A11, U1.1 (A11), U2.1 (A11)
A12: J1.A12, U1.12 (A12), U2.12 (A12)
A13: J1.A13, U5.2 (A0), U5.13 (A1), U6.2, U6.5, U6.10, U6.13, U7.2, U7.5
A14: J1.A14, U4.2 (A1)
A15: J1.A15, U4.3 (A2)
B0: U3.2 (Q0), U6.1
B1: U3.5 (Q1), U6.4
B2: U3.6 (Q2), U6.9
B3: U3.9 (Q3), U6.12
B4: U3.12 (Q4), U7.1
B5: U3.15 (Q5), U7.4
B6: U3.16 (Q6), U5.14 (A0)
BANKCLK: U3.11 (Cp), U5.5 (O1)
CE1B: U1.30 (~CE), U8.4
CE2B: U2.30 (~CE), U5.11 (O1), U8.2
D0: J1.D0, U1.21 (DQ0), U2.21 (DQ0), U3.3 (D0)
D1: J1.D1, U1.22 (DQ1), U2.22 (DQ1), U3.4 (D1)
D2: J1.D2, U1.23 (DQ2), U2.23 (DQ2), U3.7 (D2)
D3: J1.D3, U1.25 (DQ3), U2.25 (DQ3), U3.8 (D3)
D4: J1.D4, U1.26 (DQ4), U2.26 (DQ4), U3.13 (D4)
D5: J1.D5, U1.27 (DQ5), U2.27 (DQ5), U3.14 (D5)
D6: J1.D6, U1.28 (DQ6), U2.28 (DQ6), U3.17 (D6)
D7: J1.D7, U1.29 (DQ7), U2.29 (DQ7), U3.18 (D7)
FA13: U1.4 (A13), U2.4 (A13), U6.3
FA14: U1.5 (A14), U2.5 (A14), U6.6
FA15: U1.11 (A15), U2.11 (A15), U6.8
FA16: U1.10 (A16), U2.10 (A16), U6.11
FA17: U1.6 (A17), U2.6 (A17), U7.3
FA18: U1.9 (A18), U2.9 (A18), U7.6
GND: C1.2, C2.2, C3.2, C4.2, C5.2, C6.2, C7.2, C8.2, C9.2, J1.EXP0, J1.EXP1, J1.GND, U1.24 (VSS), U2.24 (VSS), U3.10 (GND), U4.4 (~E0), U4.5 (~E1), U4.8 (GND), U5.3 (A1), U5.8 (GND), U5.15 (E), U6.7 (GND), U7.7 (GND), U7.9, U7.10, U7.12, U7.13, U8.3 (GND)
unnamed: U4.9 (~Y6), U5.1 (E)
OEB: U1.32 (~OE), U2.32 (~OE), U4.7 (~Y7)
PHI2: J1.PHI2, U4.6 (E2)
RESB: J1.RESB, U3.1 (~Mr)
RWB: J1.RWB, U4.1 (A0)
VCC: C1.1, C2.1, C3.1, C4.1, C5.1, C6.1, C7.1, C8.1, C9.1, J1.VCC, U1.8 (VDD), U2.8 (VDD), U3.20 (VCC), U4.16 (VCC), U5.16 (VCC), U6.14 (VCC), U7.14 (VCC), U8.5 (VCC)
WEB: U1.7 (~WE), U2.7 (~WE), U5.4 (O0)

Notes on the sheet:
High address: FA = B OR A13
Secondary flash (DNP by default)
Address decode
Memory map $C000-$DFFF read: 8K window write: flash WEB (JEDEC command cycles) $E000-$FFFF read: U1 bank 63 write: bank register Bank register (write-only, cleared by RESB) B0-B5 8K bank within a flash chip B6 0 = U1 (primary), 1 = U2 (secondary) B7 unused Build variants 512KB U1 = SST39SF040, U2 +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
Primary flash
Bank register
Pins 4 and 6 (EXP1, EXP0) ground HRDB (High ROM disable bar), which takes $C000-$FFFF from the ROM.

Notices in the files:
README.md:
License:
Hardware designs are released under the [CERN Open Hardware Licence Version 2 – Permissive](https://ohwr.org/cern_ohl_p_v2.txt).
Firmware is released under the [MIT License](./Firmware/IB%20Controller/LICENSE).
Hardware/Flash Cart/Rev 1.1/Flash Cart.kicad_pcb:
© 2026 A.C. Wright Design | acwrightdesign.com | Rev 1.1
Hardware/Input Board/Rev 1.1/Input Board.kicad_pcb:
© 2024 A.C. Wright Design | acwrightdesign.com | Rev 1.1
Hardware/ROM Cart/Rev 1.1/ROM Cart.kicad_pcb:
© 2025 A.C. Wright Design | acwrightdesign.com | Rev 1.1
